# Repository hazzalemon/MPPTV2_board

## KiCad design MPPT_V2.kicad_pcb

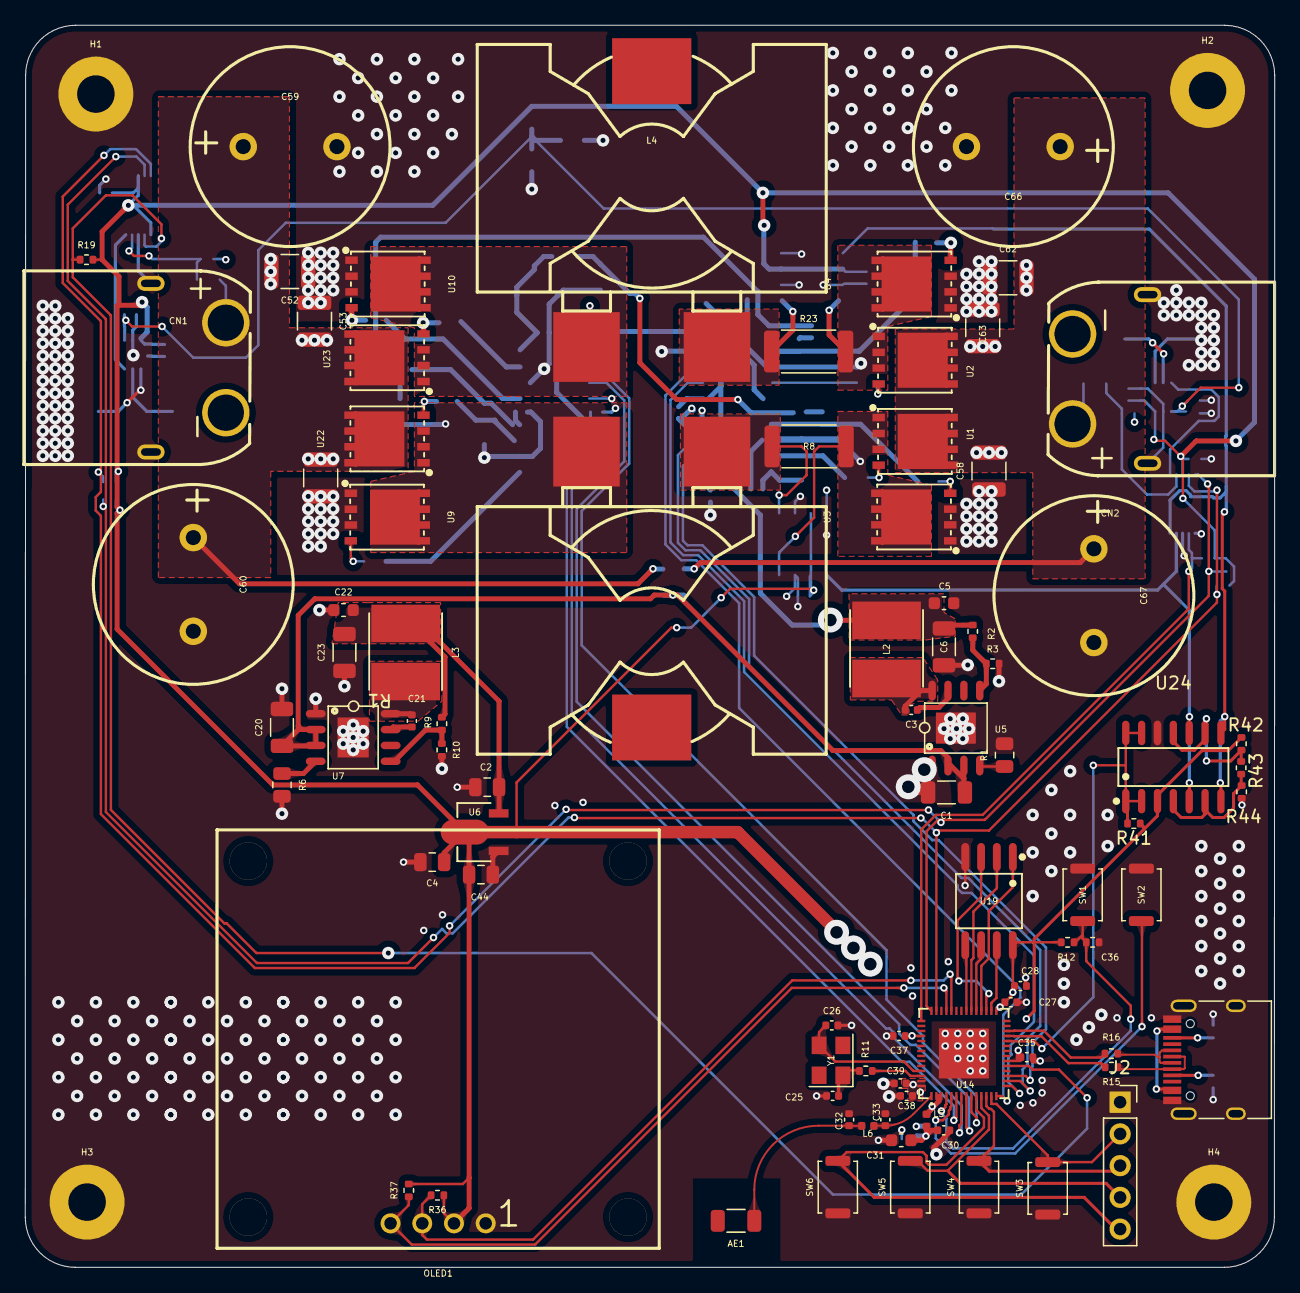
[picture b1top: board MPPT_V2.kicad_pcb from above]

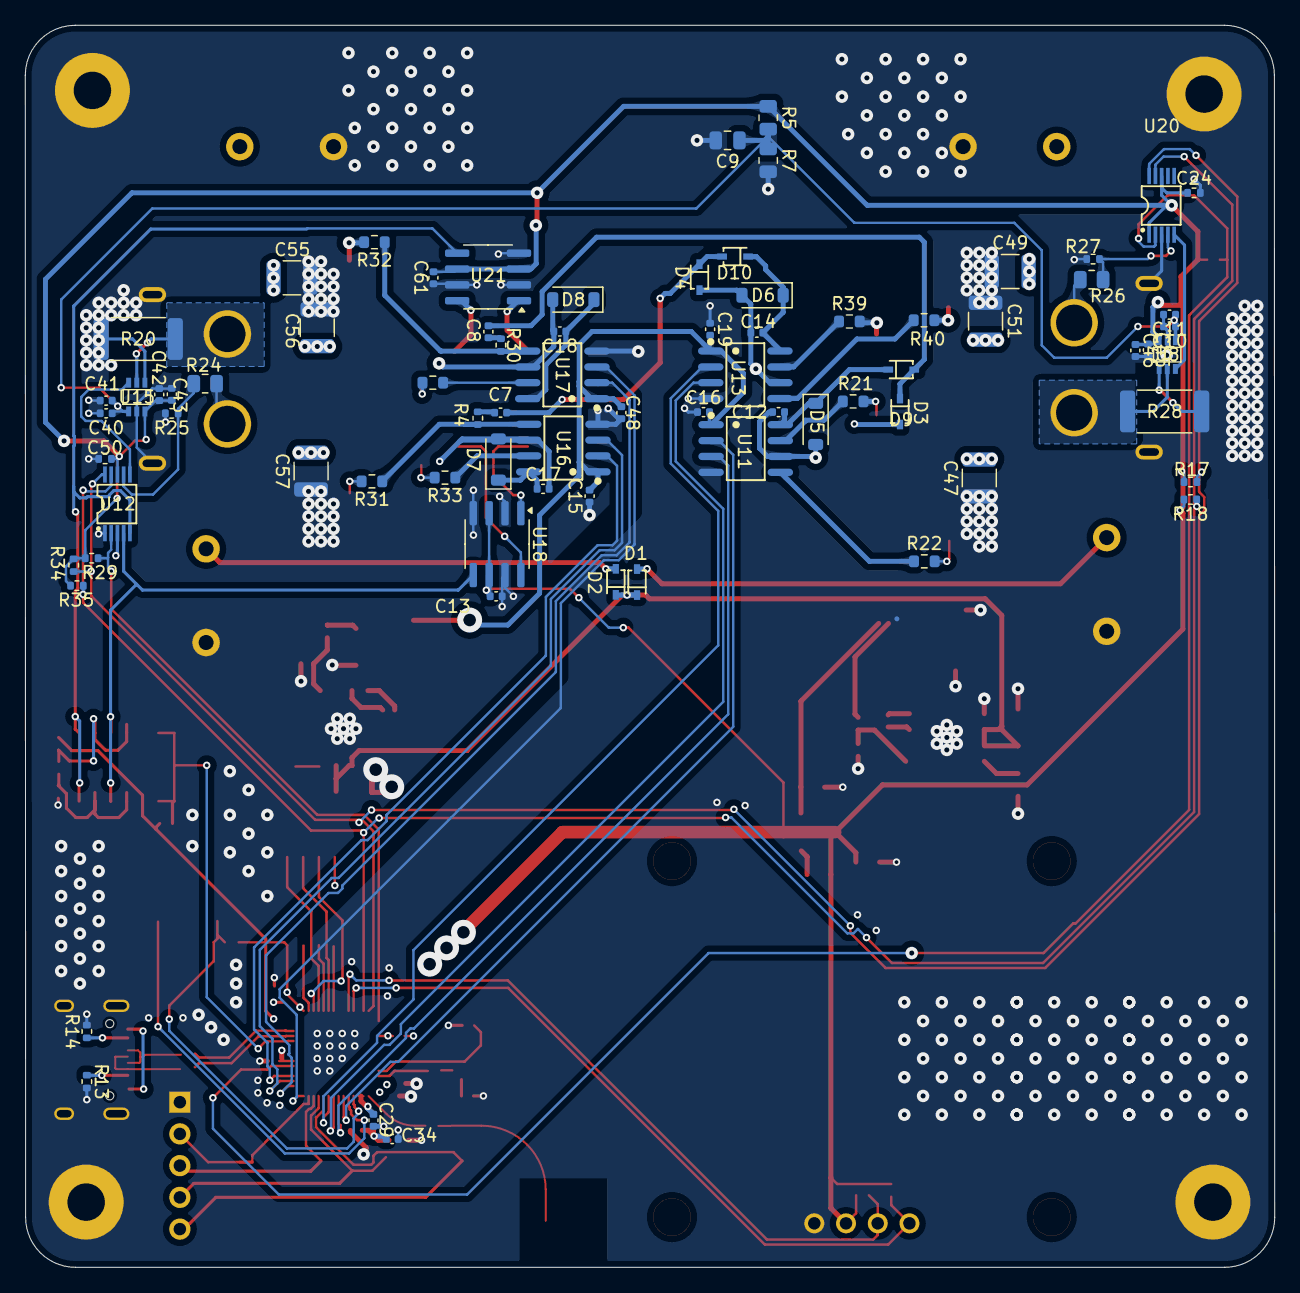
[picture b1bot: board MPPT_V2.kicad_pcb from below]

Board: 4 copper layers, 100.0 x 99.4 mm, 166 parts (76 on the bottom side), 96 nets.

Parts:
AE1: Antenna_Shield; R_1206_3216Metric
C1, C20: 2.2u; C_1206_3216Metric
C2, C4, C9, C44: 10u; C_0805_2012Metric
C3, C21: 2n; C_0402_1005Metric
C5, C22: 2.2u; C_0603_1608Metric
C6, C23: 47u; C_1206_3216Metric
C7, C8, C12, C14, C17, C18: 300n; C_0402_1005Metric
C10, C11, C13, C27, C29, C30, C35, C40, C41, C42, C43, C45, C46, C61: 100n; C_0402_1005Metric
C15, C16, C19, C28, C31, C38, C48: 1u; C_0402_1005Metric
C24, C50: 100n; R_0402_1005Metric
C25, C26, C32, C33: C_Small; C_0402_1005Metric
C34: 10u; C_0603_1608Metric
C36: 1u; R_0402_1005Metric
C37: 0.1u; C_0402_1005Metric
C39: 100p; C_0402_1005Metric
C47, C49, C51, C52, C53, C54, C55, C56, C57, C58, C62, C63: 10u; C_1210_3225Metric
C59, C60, C66, C67: 470u; CAP-TH_BD16.0-P7.50-D1.2-FD
CN1, CN2: XT60PW-M; CONN-TH_XT60PW-M
D1, D2, D3, D4, D9, D10: B16WS_C7420327; SOD-323_L1.7-W1.3-LS2.5-FD
D5, D6, D7, D8: D_Zener; D_SOD-123
H1, H2, H3, H4: MountingHole_Pad; MountingHole_3mm_Pad
J1: USB_C_Receptacle_USB2.0_16P; USB_C_Receptacle_HRO_TYPE-C-31-M-12
J2: Conn_01x05; PinSocket_1x05_P2.54mm_Vertical
L1, L4: FC-SE2918-100M-28A; IND-SMD_3P-L27.9-W19.7-P10.43-LS27.9-BL-A
L2, L3: 220u; IND-SMD_L5.8-W5.2
L5, L6: 2n; L_0402_1005Metric
OLED1: HS13L03W2C01; OLED-TH_L35.4-W33.5_HS13L03W2C01
R1, R5, R6, R7, R24, R26: 100k; R_0805_2012Metric
R2: 453k; R_0402_1005Metric
R3: 49.9k; R_0402_1005Metric
R4, R30: 500; R_0402_1005Metric
R8, R23: 1m; R_2512_6332Metric
R9: 200k; R_0402_1005Metric
R10: 63k; R_0402_1005Metric
R11: R_Small; R_0402_1005Metric
R12, R15, R16, R17, R18, R19, R29, R34, R35: 10k; R_0402_1005Metric
R13, R14, R36, R37: 5.1k; R_0402_1005Metric
R20, R28: 0.5m; R_2512_6332Metric
R21, R22, R31, R32, R33, R38, R39, R40: 4.2; R_0603_1608Metric
R25, R27, R41, R42, R43, R44: 4.125k; R_0402_1005Metric
SW1, SW2, SW3, SW4, SW5, SW6: SW_Push; SW_Push_SPST_NO_Alps_SKRK
U1, U2, U3, U4, U9, U10, U22, U23: S130N10LF; TDFN-8_L5.9-W5.2-P1.27-LS6.2-BL
U5, U7: LM5164DDAR; SO-8_L4.9-W3.9-P1.27-LS6.0-BL-EP
U6: AMS1117-3.3(XBLW); SOT-89-3_L4.5-W2.5-P1.50-LS4.2-BR
U8, U15: TP181A1-CR; SC70-6_L2.1-W1.3-P0.65-LS2.3-BL
U11, U13, U16, U17: XJNG2103; SOIC-8_L4.9-W3.9-P1.27-LS6.0-BL
U12, U20: ADS1015IDGSR; VSSOP-10_L3.0-W3.0-P0.50-LS4.9-BL
U14: ESP32-S3(FN8); QFN-56_L7.0-W7.0-P0.40-TL-EP4.0
U18, U21: INA240A2D; SOIC-8_3.9x4.9mm_P1.27mm
U19: W25Q128JVSIQTR; SOIC-8_L5.3-W5.3-P1.27-LS8.0-BL
U24: LM2901; SOP-14_L8.6-W3.9-P1.27-LS6.0-BL-1
Y1: Crystal_GND24_Small; Crystal_SMD_SeikoEpson_FA238V-4Pin_3.2x2.5mm

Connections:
+3.3V: C4.1, C13.1, C24.1, C27.1, C28.1, C30.1, C31.1, C34.1, C35.1, C37.1, C38.1, C39.1, C42.1, C43.1, C44.1, C45.1, C46.1, C50.1, C61.1, L5.1, OLED1.2 (VCC), R5.1, R12.1, R17.2, R18.2, R19.2, R29.2, R34.2, R35.2, R36.1, R37.2, R41.1, R42.1, U6.2 (VOUT), U8.3 (V+), U12.8 (VDD), U14.20 (VDD3P3_RTC), U14.29 (VDD_SPI), U14.46 (VDD3P3_CPU), U14.55 (VDDA), U14.56 (VDDA), U15.3 (V+), U18.3 (REF2), U18.6 (V+), U19.8 (VCC), U20.1 (ADDR), U20.8 (VDD), U21.3 (REF2), U21.6 (V+), U24.3 (V+)
+5V: C2.1, C22.2, C23.2, L3.2, R9.1, U6.3 (VIN)
+12V: C5.2, C6.2, C15.2, C16.2, C19.2, C48.2, L2.2, R2.1, U11.1 (VCC), U13.1 (VCC), U16.1 (VCC), U17.1 (VCC)
/CUR_PHASE_A: U12.4 (AIN0), U18.5, U24.5 (+), U24.10 (-)
/CUR_PHASE_B: U12.5 (AIN1), U21.5, U24.7 (+), U24.8 (-)
/FETs1/IN_GATE_HI: R39.1, U13.7 (HO)
/FETs1/IN_GATE_LOW: R40.1, U13.5 (LO)
/FETs1/IN_GATE_SW: C14.2, D4.1 (A), D6.2 (A), L4.2, U10.5 (D), U10.6 (D), U10.7 (D), U10.8 (D), U10.9 (D), U13.6 (VS), U23.1 (S), U23.2 (S), U23.3 (S)
/FETs1/OUT_GATE_HI: R38.1, U17.7 (HO)
/FETs1/OUT_GATE_LOW: R30.2, R32.1, U17.5 (LO)
/FETs1/OUT_GATE_SW: C18.2, D8.2 (A), R23.2, U2.1 (S), U2.2 (S), U2.3 (S), U4.5 (D), U4.6 (D), U4.7 (D), U4.8 (D), U4.9 (D), U17.6 (VS), U21.8 (+)
/FETs/IN_GATE_HI: R21.1, U11.7 (HO)
/FETs/IN_GATE_LOW: R22.1, U11.5 (LO)
/FETs/IN_GATE_SW: C12.2, D3.1 (A), D5.2 (A), L1.2, U9.5 (D), U9.6 (D), U9.7 (D), U9.8 (D), U9.9 (D), U11.6 (VS), U22.1 (S), U22.2 (S), U22.3 (S)
/FETs/OUT_GATE_HI: R33.1, U16.7 (HO)
/FETs/OUT_GATE_LOW: R4.2, R31.1, U16.5 (LO)
/FETs/OUT_GATE_SW: C17.2, D7.2 (A), R8.2, U1.1 (S), U1.2 (S), U1.3 (S), U3.5 (D), U3.6 (D), U3.7 (D), U3.8 (D), U3.9 (D), U16.6 (VS), U18.8 (+)
/IN_CUR: U8.6 (OUT), U20.5 (AIN1)
/MCU/ADC_READY: R29.1, U12.2 (ALERT/RDY), U14.43 (GPIO38)
/MCU/ADC_READY2: R19.1, U14.19 (GPIO14), U20.2 (ALERT/RDY)
/MCU/D+: R16.2, U14.26 (GPIO20)
/MCU/D-: R15.2, U14.25 (GPIO19)
/MCU/IN_HI_PWMA: U11.2 (HIN), U14.6 (GPIO1)
/MCU/IN_HI_PWMB: U13.2 (HIN), U14.9 (GPIO4)
/MCU/IN_LO_PWMA: U11.3 (~LIN), U14.7 (GPIO2)
/MCU/IN_LO_PWMB: U13.3 (~LIN), U14.8 (GPIO3)
/MCU/IO_BTN1: J2.2, SW3.2, U14.13 (GPIO8)
/MCU/IO_BTN2: J2.3, SW4.2, U14.12 (GPIO7)
/MCU/IO_BTN3: J2.4, SW5.2, U14.11 (GPIO6)
/MCU/IO_BTN4: J2.5, SW6.2, U14.10 (GPIO5)
/MCU/OUT_HI_PWMA: U14.17 (GPIO12), U16.2 (HIN)
/MCU/OUT_HI_PWMB: U14.15 (GPIO10), U17.2 (HIN)
/MCU/OUT_LO_PWMA: U14.16 (GPIO11), U16.3 (~LIN)
/MCU/OUT_LO_PWMB: U14.14 (GPIO9), U17.3 (~LIN)
/MCU/SCL: R17.1, R34.1, U12.10 (SCL), U14.42 (GPIO37), U20.10 (SCL)
/MCU/SCL_DISPL: OLED1.3 (SCL), R36.2, U14.38 (GPIO33)
/MCU/SDA: R18.1, R35.1, U12.9 (SDA), U14.41 (GPIO36), U20.9 (SDA)
/MCU/SDA_DISPL: OLED1.4 (SDA), R37.1, U14.39 (GPIO34)
/MCU/SPICLK: U14.33 (SPICLK), U19.6 (CLK)
/MCU/SPICS0: U14.32 (SPICS0), U19.1 (~CS)
/MCU/SPID: U14.35 (SPID), U19.5 (DI)
/MCU/SPIHD: U14.30 (SPIHD), U19.7 (IO3)
/MCU/SPIQ: U14.34 (SPIQ), U19.2 (DO)
/MCU/SPIWP: U14.31 (SPIWP), U19.3 (IO2)
/MCU/USB_D+: J1.A6 (D+), J1.B6 (D+), R16.1
/MCU/USB_D-: J1.A7 (D-), J1.B7 (D-), R15.1
/Mid_rail_ref: C9.1, C10.1, C11.1, C40.1, C41.1, R5.2, R7.1, U8.1 (REF), U15.1 (REF)
/OCP: R41.2, U14.24 (GPIO18), U24.1, U24.2, U24.13, U24.14
/OUT_CUR: U12.6 (AIN2), U15.6 (OUT)
/Vin_sense: R26.2, R27.1, U20.4 (AIN0)
/Vout_sense: R24.2, R25.1, U12.7 (AIN3)
/fet_drivers_A/Charge_pump_IN: C8.1, D3.2 (K), D9.1 (A)
/fet_drivers_A/Charge_pump_OUT: C7.1, D4.2 (K), D10.1 (A)
/max_cur_neg: R43.2, R44.1, U24.4 (-), U24.6 (-)
/max_cur_pos: R42.2, R43.1, U24.9 (+), U24.11 (+)
GND: C1.2, C2.2, C4.2, C5.1, C6.1, C9.2, C10.2, C11.2, C13.2, C15.1, C16.1, C19.1, C20.2, C22.1, C23.1, C24.2, C25.2, C26.2, C27.2, C28.2, C29.2, C30.2, C31.2, C32.2, C33.2, C34.2, C35.2, C36.2, C37.2, C38.2, C39.2, C40.2, C41.2, C42.2, C43.2, C44.2, C45.2, C46.2, C47.1, C48.1, C49.1, C50.2, C51.1, C52.1, C53.1, C54.1, C55.1, C56.1, C57.1, C58.1, C59.2, C60.2, C61.2, C62.1, C63.1, C66.2, C67.2, CN1.3, CN1.4, CN2.3, CN2.4, H1.1, H2.1, H3.1, H4.1, J1.A1 (GND), J1.A12 (GND), J1.B1 (GND), J1.B12 (GND), J1.S1 (SHIELD), J2.1, OLED1.1 (GND), R1.2, R3.2, R6.2, R7.2, R10.2, R13.2, R14.2, R20.2, R25.2, R27.2, R28.2, R44.2, SW1.1, SW2.1, SW3.1, SW4.1, SW5.1, SW6.1, U3.1 (S), U3.2 (S), U3.3 (S), U4.1 (S), U4.2 (S), U4.3 (S), U5.1 (GND), U5.9 (EP), U6.1 (GND), U7.1 (GND), U7.9 (EP), U8.2 (GND), U8.4 (IN+), U9.1 (S), U9.2 (S), U9.3 (S), U10.1 (S), U10.2 (S), U10.3 (S), U11.4 (COM), U12.1 (ADDR), U12.3 (GND), U13.4 (COM), U14.57 (EP), U15.2 (GND), U15.4 (IN+), U16.4 (COM), U17.4 (COM), U18.2 (GND), U18.4 (GND), U18.7 (REF1), U19.4 (GND), U20.3 (GND), U21.2 (GND), U21.4 (GND), U21.7 (REF1), U24.12 (V-)
unnamed: AE1.1 (A), C32.1, L6.1
unnamed: C7.2, R4.1
unnamed: C8.2, R30.1
unnamed: C25.1, R11.2, Y1.1
unnamed: C29.1, L5.2, U14.2 (VDD3P3), U14.3 (VDD3P3)
unnamed: CN1.1 (-), R28.1, U8.5 (IN-)
unnamed: CN2.1 (-), R20.1, U15.5 (IN-)
unnamed: C1.1, C20.1, D1.2 (K), D2.2 (K), U5.2 (VIN), U5.3 (EN/UVLO), U7.2 (VIN), U7.3 (EN/UVLO)
unnamed: C12.1, D5.1 (K), D9.2 (K), U11.8 (VB)
unnamed: C17.1, D7.1 (K), U16.8 (VB)
unnamed: C18.1, D8.1 (K), U17.8 (VB)
unnamed: C14.1, D6.1 (K), D10.2 (K), U13.8 (VB)
unnamed: J1.A5 (CC1), R13.1
unnamed: J1.B5 (CC2), R14.1
unnamed: J1.A4 (VBUS), J1.A9 (VBUS), J1.B4 (VBUS), J1.B9 (VBUS)
unnamed: R33.2, U1.4 (G)
unnamed: R38.2, U2.4 (G)
unnamed: R31.2, U3.4 (G)
unnamed: R32.2, U4.4 (G)
unnamed: C3.1, U5.7 (BST)
unnamed: R2.2, R3.1, U5.5 (FB)
unnamed: R1.1, U5.4 (RON)
unnamed: C3.2, L2.1, U5.8 (SW)
unnamed: C21.1, U7.7 (BST)
unnamed: R9.2, R10.1, U7.5 (FB)
unnamed: R6.1, U7.4 (RON)
unnamed: C21.2, L3.1, U7.8 (SW)
unnamed: R22.2, U9.4 (G)
unnamed: R40.2, U10.4 (G)
unnamed: C36.1, R12.2, SW1.2, U14.4 (CHIP_PU)
unnamed: SW2.2, U14.5 (GPIO0)
unnamed: C33.1, L6.2, U14.1 (LNA_IN)
unnamed: C26.1, U14.53 (XTAL_N), Y1.3
unnamed: R11.1, U14.54 (XTAL_P)
unnamed: L1.1, R8.1, U18.1 (-)
unnamed: L4.1, R23.1, U21.1 (-)
unnamed: R21.2, U22.4 (G)
unnamed: R39.2, U23.4 (G)
VDD: C47.2, C49.2, C51.2, C52.2, C53.2, C54.2, C59.1, C60.1, CN1.2 (+), D1.1 (A), R26.1, U22.5 (D), U22.6 (D), U22.7 (D), U22.8 (D), U22.9 (D), U23.5 (D), U23.6 (D), U23.7 (D), U23.8 (D), U23.9 (D)
Vout: C55.2, C56.2, C57.2, C58.2, C62.2, C63.2, C66.1, C67.1, CN2.2 (+), D2.1 (A), R24.1, U1.5 (D), U1.6 (D), U1.7 (D), U1.8 (D), U1.9 (D), U2.5 (D), U2.6 (D), U2.7 (D), U2.8 (D), U2.9 (D)

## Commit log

2024-09-26 init
